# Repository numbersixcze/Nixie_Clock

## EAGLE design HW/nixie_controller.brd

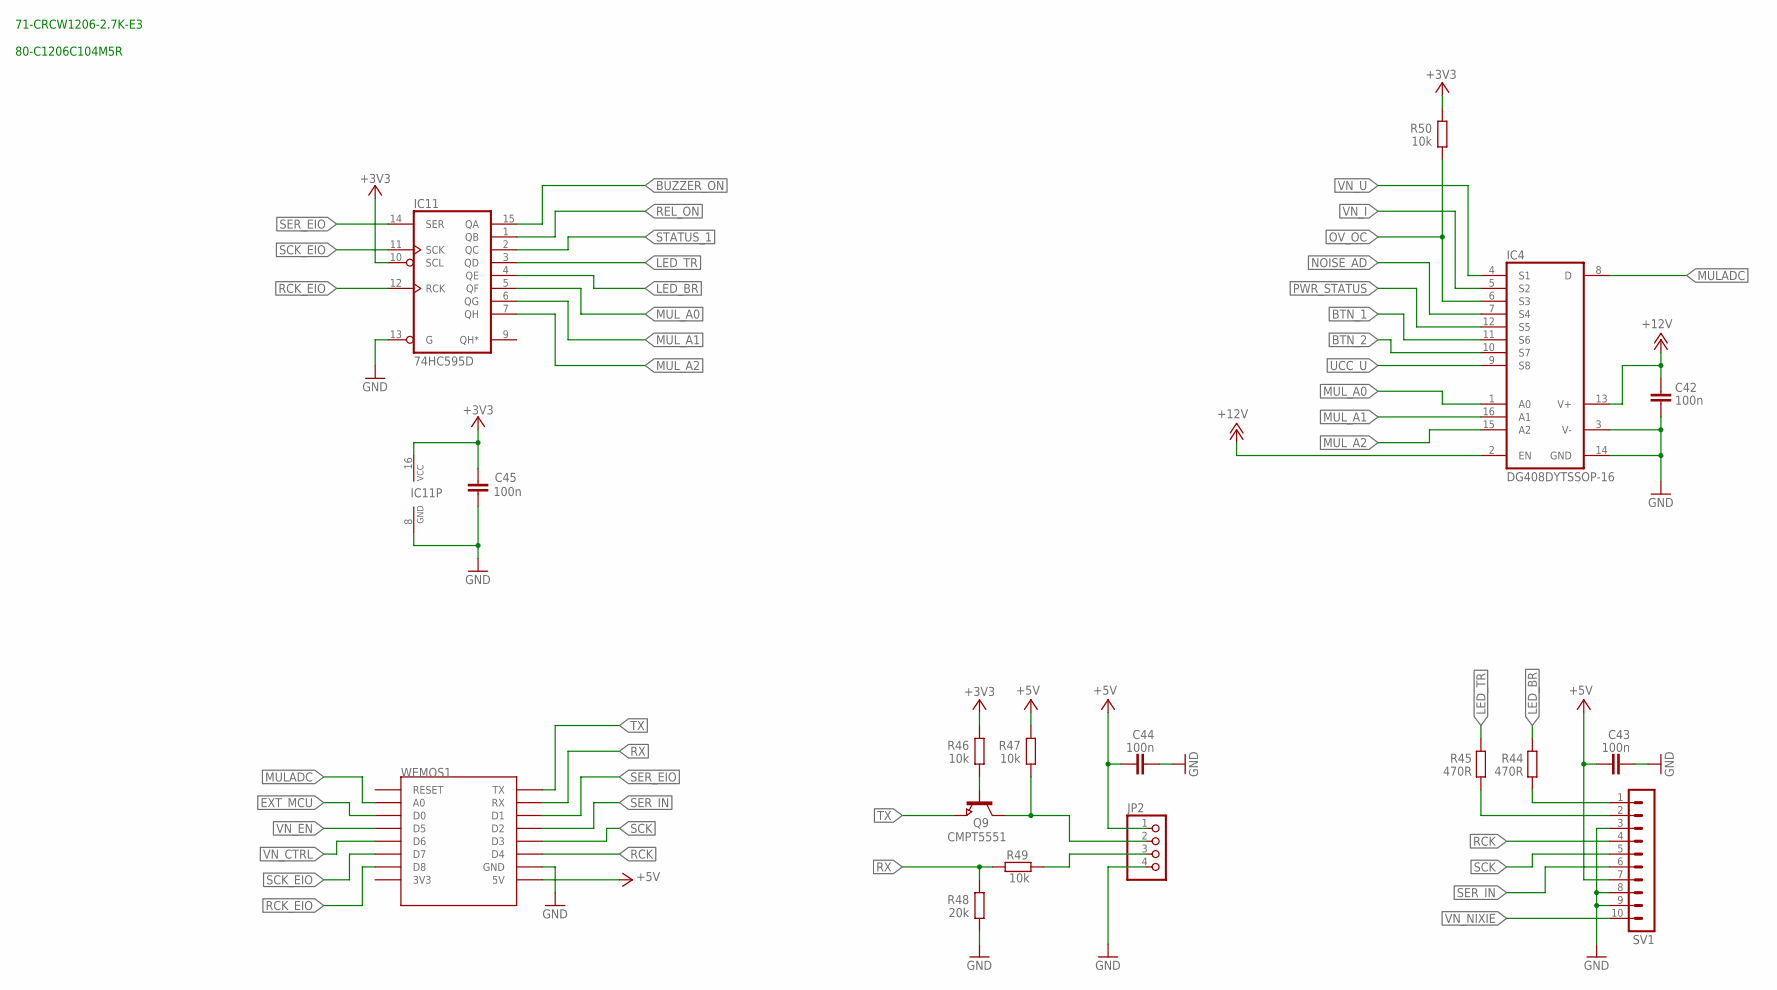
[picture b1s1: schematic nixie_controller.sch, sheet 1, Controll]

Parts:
C42, C43, C44, C45: 100n; C1206
IC4: DG408DYTSSOP-16; TSSOP16
IC11: 74HC595D; SO16
JP2: PINHD-1X4/90; 1X04/90
Q9: CMPT5551; SOT23
R44, R45: 470R; R1206
R46, R47, R49, R50: 10k; R1206
R48: 20k; R1206
SV1: MA10-1
WEMOS1: WEMOS-D1-MINI

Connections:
+3V3: C45.1, IC11.10 (SCL), IC11.16 (VCC), R46.1, R50.1; also elsewhere on the board
+5V: C43.1, C44.1, JP2.1, R47.1, SV1.7, WEMOS1.5V; also elsewhere on the board
+12V: C42.1, IC4.2 (EN), IC4.13 (V+); also elsewhere on the board
BTN_1: IC4.11 (S6); also elsewhere on the board
BTN_2: IC4.10 (S7); also elsewhere on the board
BUZZER_ON: IC11.15 (QA); also elsewhere on the board
EXT_MCU: WEMOS1.D0; also elsewhere on the board
GND: C42.2, C43.2, C44.2, C45.2, IC4.3 (V-), IC4.14 (GND), IC11.8 (GND), IC11.13 (G), JP2.4, R48.2, SV1.3, SV1.8, SV1.9, WEMOS1.GND; also elsewhere on the board
LED_B: R45.2, SV1.2
LED_BR: IC11.4 (QE), R44.1
LED_T: R44.2, SV1.1
LED_TR: IC11.3 (QD), R45.1
MULADC: IC4.8 (D), WEMOS1.A0
MUL_A0: IC4.1 (A0), IC11.5 (QF)
MUL_A1: IC4.16 (A1), IC11.6 (QG)
MUL_A2: IC4.15 (A2), IC11.7 (QH)
unnamed: Q9.1 (B), R46.2
NOISE_AD: IC4.7 (S4); also elsewhere on the board
OV_OC: IC4.6 (S3), R50.2; also elsewhere on the board
PWR_STATUS: IC4.12 (S5); also elsewhere on the board
RCK: SV1.4, WEMOS1.D4
RCK_EIO: IC11.12 (RCK), WEMOS1.D8
REL_ON: IC11.1 (QB); also elsewhere on the board
RX: R48.1, R49.1, WEMOS1.RX
RX_IN: JP2.3, R49.2
SCK: SV1.5, WEMOS1.D3
SCK_EIO: IC11.11 (SCK), WEMOS1.D7
SER_EIO: IC11.14 (SER), WEMOS1.D1
SER_IN: SV1.6, WEMOS1.D2
STATUS_1: IC11.2 (QC); also elsewhere on the board
TX: Q9.2 (E), WEMOS1.TX
TX_IN: JP2.2, Q9.3 (C), R47.2
UCC_U: IC4.9 (S8); also elsewhere on the board
VN_CTRL: WEMOS1.D6; also elsewhere on the board
VN_EN: WEMOS1.D5; also elsewhere on the board
VN_I: IC4.5 (S2); also elsewhere on the board
VN_NIXIE: SV1.10; also elsewhere on the board
VN_U: IC4.4 (S1); also elsewhere on the board

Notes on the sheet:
71-CRCW1206-2.7K-E3 80-C1206C104M5R

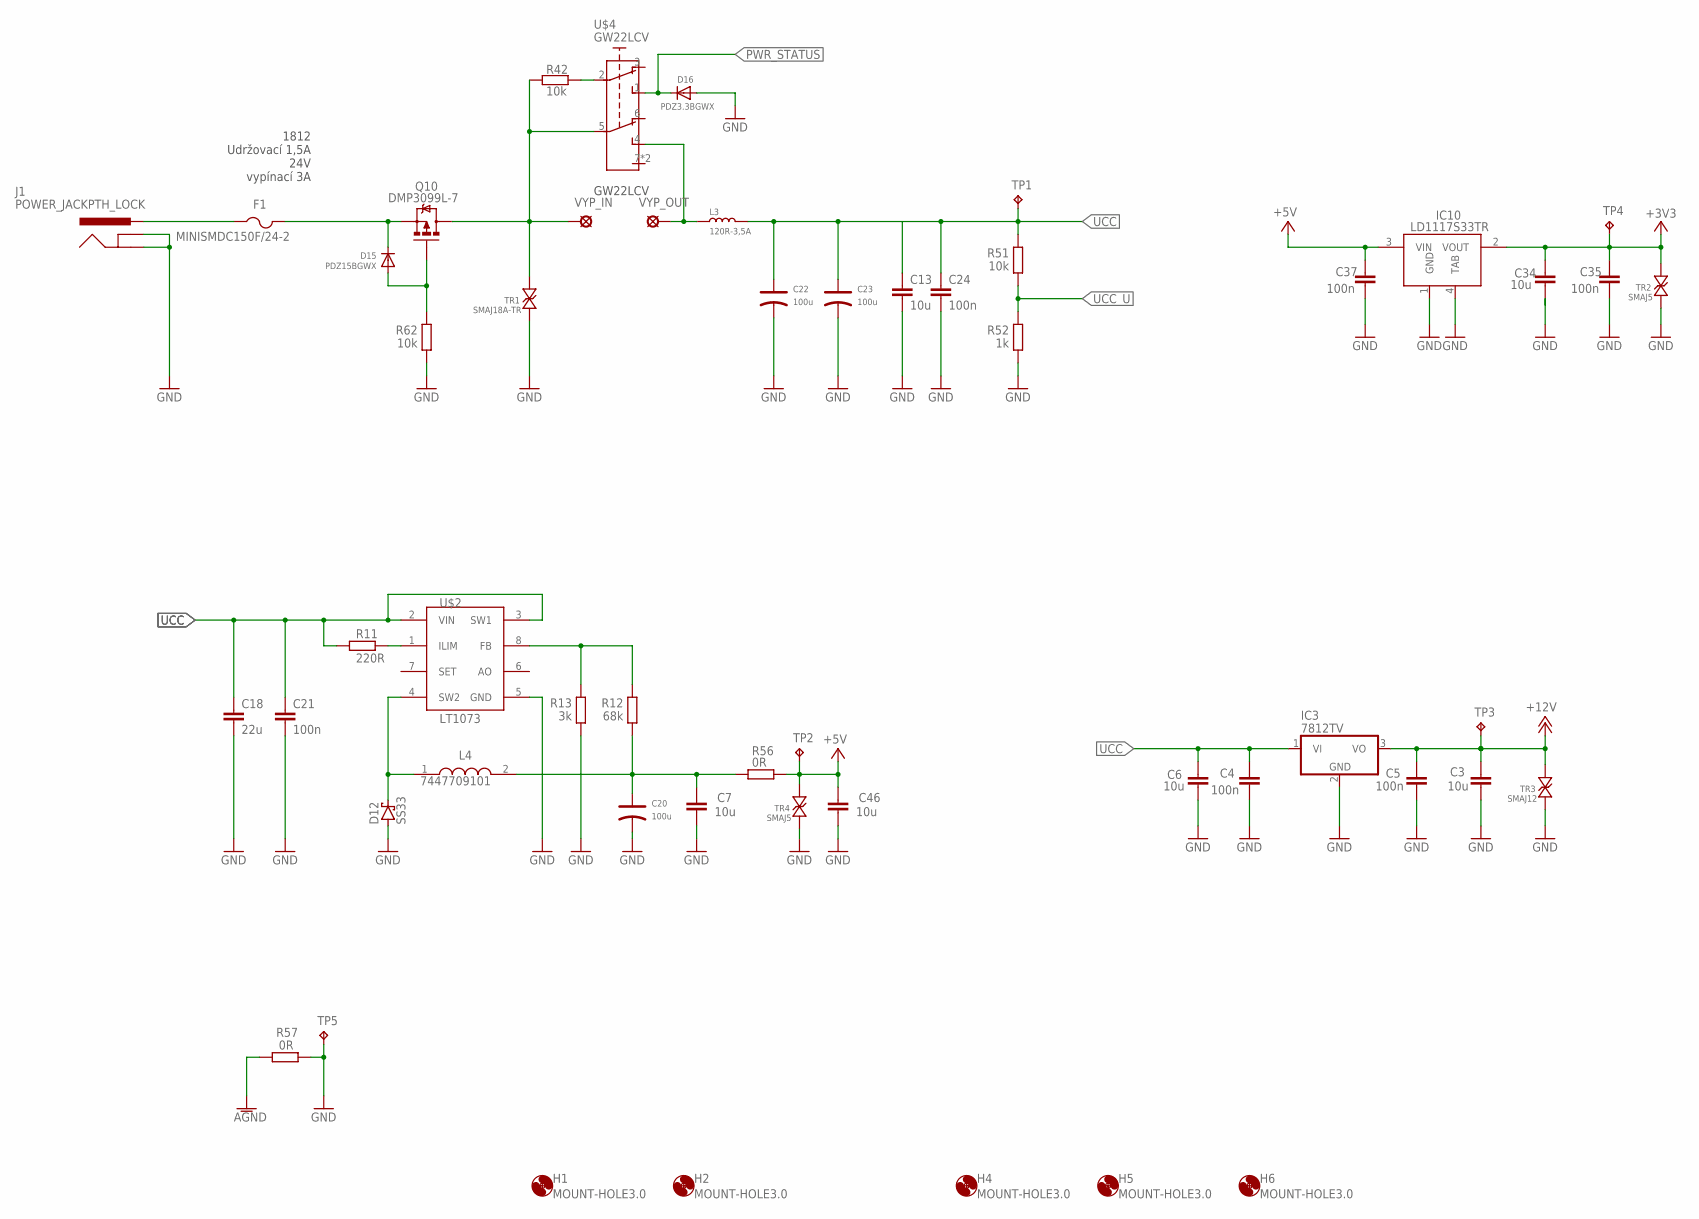
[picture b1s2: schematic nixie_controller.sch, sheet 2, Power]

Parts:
C3, C6, C7, C13, C34, C46: 10u; C1206
C4, C5, C21, C24, C35, C37: 100n; C1206
C18: 22u; C1206
C20, C22, C23: 100u; ELECTRO-SMD-C-6MM
D12: SS33; SMC
D15: PDZ15BGWX; SOD-123
D16: PDZ3.3BGWX; SOD-123
F1: MINISMDC150F/24-2; 1812
H1, H2, H4, H5, H6: MOUNT-HOLE3.0; 3,0
IC3: 7812TV; TO220V
IC10: LD1117S33TR; SOT230P700X180-4N
J1: POWER_JACKPTH_LOCK; POWER_JACK_PTH_LOCK
L3: 120R-3,5A; L0805
L4: 7447709101; INDM120120X1000N
Q10: DMP3099L-7; SOT23-3
R11: 220R; R1206
R12: 68k; R1206
R13: 3k; R1206
R42, R51, R62: 10k; R1206
R52: 1k; R1206
R56, R57: 0R; R1206
TP1, TP2, TP3, TP4, TP5: TPB1,27; B1,27
TR1: SMAJ18A-TR; DO214AC+MINIMELF_BIDIR
TR2, TR4: SMAJ5; DO214AC+MINIMELF_BIDIR
TR3: SMAJ12; DO214AC+MINIMELF_BIDIR
U$2: LT1073; SOIC127P599X175-8
U$4: GW22LCV
VYP_IN: LSP11
VYP_OUT: LSP11

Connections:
+3V3: C34.1, C35.1, IC10.2 (VOUT), TP4.TP, TR2.P$2; also elsewhere on the board
+5V: C37.1, C46.1, IC10.3 (VIN), R56.1, TP2.TP, TR4.P$2; also elsewhere on the board
+12V: C3.1, C5.1, IC3.3 (VO), TP3.TP, TR3.P$2; also elsewhere on the board
AGND: R57.2; also elsewhere on the board
GND: C3.2, C4.2, C5.2, C6.2, C7.2, C13.2, C18.2, C20.-, C21.2, C22.-, C23.-, C24.2, C34.2, C35.2, C37.2, C46.2, D12.A, D16.A, IC3.2 (GND), IC10.1 (GND), IC10.4 (TAB), J1.GND, J1.GNDBREAK, R13.1, R52.1, R57.1, R62.1, TP5.TP, TR1.P$1, TR2.P$1, TR3.P$1, TR4.P$1, U$2.5 (GND); also elsewhere on the board
unnamed: D12.C, L4.1, U$2.4 (SW2)
unnamed: F1.1, J1.PWR
unnamed: L3.1, U$4.4 (NO1), VYP_OUT.MP
unnamed: R11.2, U$2.1 (ILIM)
unnamed: R12.2, R13.2, U$2.8 (FB)
unnamed: Q10.3 (D), R42.2, TR1.P$2, U$4.5 (COM1), VYP_IN.MP
unnamed: C7.1, C20.+, L4.2, R12.1, R56.2
unnamed: D15.C, F1.2, Q10.2 (S)
unnamed: R42.1, U$4.2 (COM)
unnamed: D15.A, Q10.1 (G), R62.2
P$1: U$4.7, U$4.8
PWR_STATUS: D16.C, U$4.1 (NO); also elsewhere on the board
UCC: C4.1, C6.1, C13.1, C18.1, C21.1, C22.+, C23.+, C24.1, IC3.1 (VI), L3.2, R11.1, R51.2, TP1.TP, U$2.2 (VIN), U$2.3 (SW1); also elsewhere on the board
UCC_U: R51.1, R52.2; also elsewhere on the board

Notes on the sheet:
1812 Udržovací 1,5A 24V vypínací 3A
GW22LCV

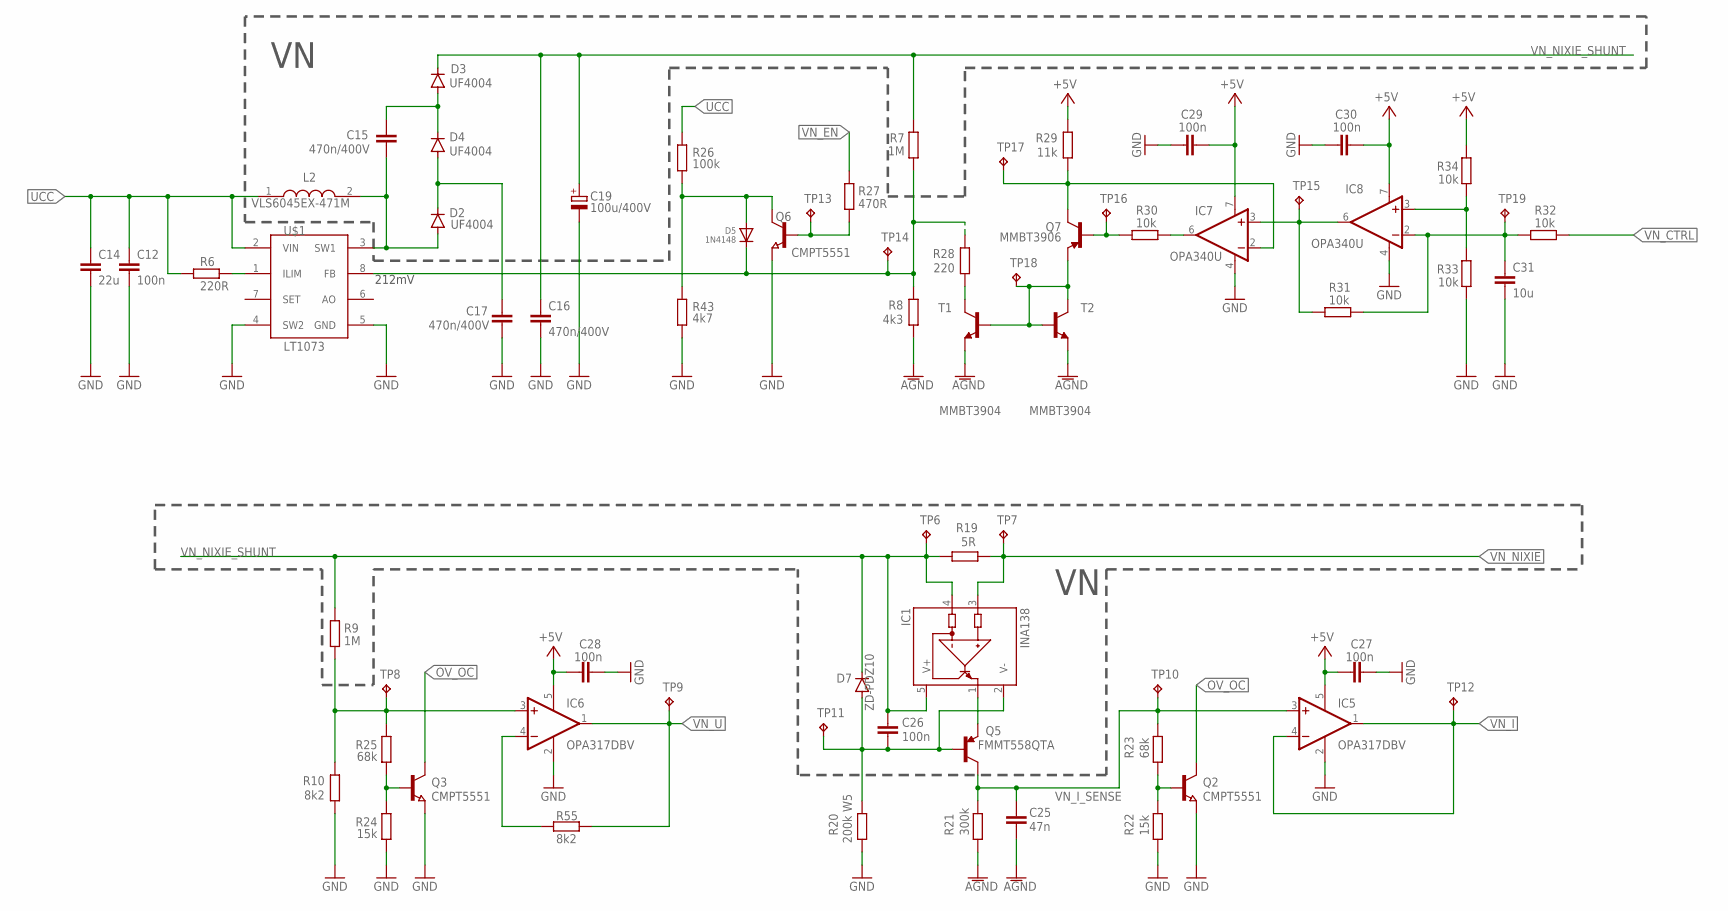
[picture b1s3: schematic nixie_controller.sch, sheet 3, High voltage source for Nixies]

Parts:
C12, C26, C27, C28, C29, C30: 100n; C1206
C14: 22u; C1206
C15, C16, C17: 470n/400V; C1812
C19: 100u/400V; E51-22
C25: 47n; C1206
C31: 10u; C1206
D2, D3, D4: UF4004; DO41-10
D5: 1N4148; SOD-123
D7: ZD-PDZ10; SOD123
IC1: INA138; SOT23-5
IC5, IC6: OPA317DBV; SOT23-5
IC7, IC8: OPA340U; SO08
L2: VLS6045EX-471M; INDPM6060X450N
Q2, Q3, Q6: CMPT5551; SOT23
Q5: FMMT558QTA; SOT23-3
Q7: MMBT3906; SOT23-3
R6: 220R; R1206
R7, R9: 1M; R1206
R8: 4k3; R1206
R10, R55: 8k2; R1206
R19: 5R; R1206
R20: 200k W5; R1206
R21: 300k; R1206
R22, R24: 15k; R1206
R23, R25: 68k; R1206
R26: 100k; R1206
R27: 470R; R1206
R28: 220; R1206
R29: 11k; R1206
R30, R31, R32, R33, R34: 10k; R1206
R43: 4k7; R1206
T1, T2: MMBT3904; SOT23-BEC
TP6, TP7, TP8, TP9, TP10, TP11, TP12, TP13, TP14, TP15, TP16, TP17, TP18, TP19: TPB1,27; B1,27
U$1: LT1073; SOIC127P599X175-8

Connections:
+5V: C27.1, C28.1, C29.1, C30.1, IC5.5 (V+), IC6.5 (V+), IC7.7 (V+), IC8.7 (V+), R29.2, R34.1; also elsewhere on the board
AGND: C25.2, R8.1, R21.2, T1.E, T2.E; also elsewhere on the board
GND: C12.2, C14.2, C16.2, C17.2, C19.-, C27.2, C28.2, C29.2, C30.2, C31.2, IC5.2 (V-), IC6.2 (V-), IC7.4 (V-), IC8.4 (V-), Q2.2 (E), Q3.2 (E), Q6.2 (E), R10.1, R20.2, R22.2, R24.2, R33.2, R43.2, U$1.4 (SW2), U$1.5 (GND); also elsewhere on the board
unnamed: IC6.4 (-IN), R55.2
unnamed: R6.2, U$1.1 (ILIM)
unnamed: C15.1, D2.A, L2.2, U$1.3 (SW1)
unnamed: C15.2, D3.A, D4.C
unnamed: C17.1, D2.C, D4.A
unnamed: Q2.1 (B), R22.1, R23.2
unnamed: Q3.1 (B), R24.1, R25.2
unnamed: Q6.1 (B), R27.2, TP13.TP
unnamed: C26.2, D7.A, IC1.2 (V-), Q5.1 (B), R20.1, TP11.TP
unnamed: IC1.1 (OUT), Q5.2 (E)
unnamed: C31.1, IC8.2 (-IN), R31.1, R32.2, TP19.TP
unnamed: R28.1, T1.C
unnamed: Q7.2 (E), T1.B, T2.B, T2.C, TP18.TP
unnamed: IC7.3 (+IN), IC8.6 (OUT), R31.2, TP15.TP
unnamed: IC8.3 (+IN), R33.1, R34.2
unnamed: Q7.1 (B), R30.2, TP16.TP
unnamed: IC7.6 (OUT), R30.1
unnamed: IC7.2 (-IN), Q7.3 (C), R29.1, TP17.TP
unnamed: D5.A, Q6.3 (C), R26.2, R43.1
OV_OC: Q2.3 (C), Q3.3 (C); also elsewhere on the board
SW_FB: D5.C, R7.1, R8.2, R28.2, TP14.TP, U$1.8 (FB)
UCC: C12.1, C14.1, L2.1, R6.1, R26.1, U$1.2 (VIN); also elsewhere on the board
VN_CTRL: R32.1; also elsewhere on the board
VN_EN: R27.1; also elsewhere on the board
VN_I: IC5.1 (OUT), IC5.4 (-IN), TP12.TP; also elsewhere on the board
VN_I_SENSE: C25.1, IC5.3 (+IN), Q5.3 (C), R21.1, R23.1, TP10.TP
VN_NIXIE: IC1.3 (IN+), R19.1, TP7.TP; also elsewhere on the board
VN_NIXIE_SHUNT: C16.1, C19.+, C26.1, D3.C, D7.C, IC1.4 (IN-), IC1.5 (V+), R7.2, R9.2, R19.2, TP6.TP
VN_U: IC6.1 (OUT), R55.1, TP9.TP; also elsewhere on the board
VN_U_SENSE: IC6.3 (+IN), R9.1, R10.2, R25.1, TP8.TP

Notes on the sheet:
212mV

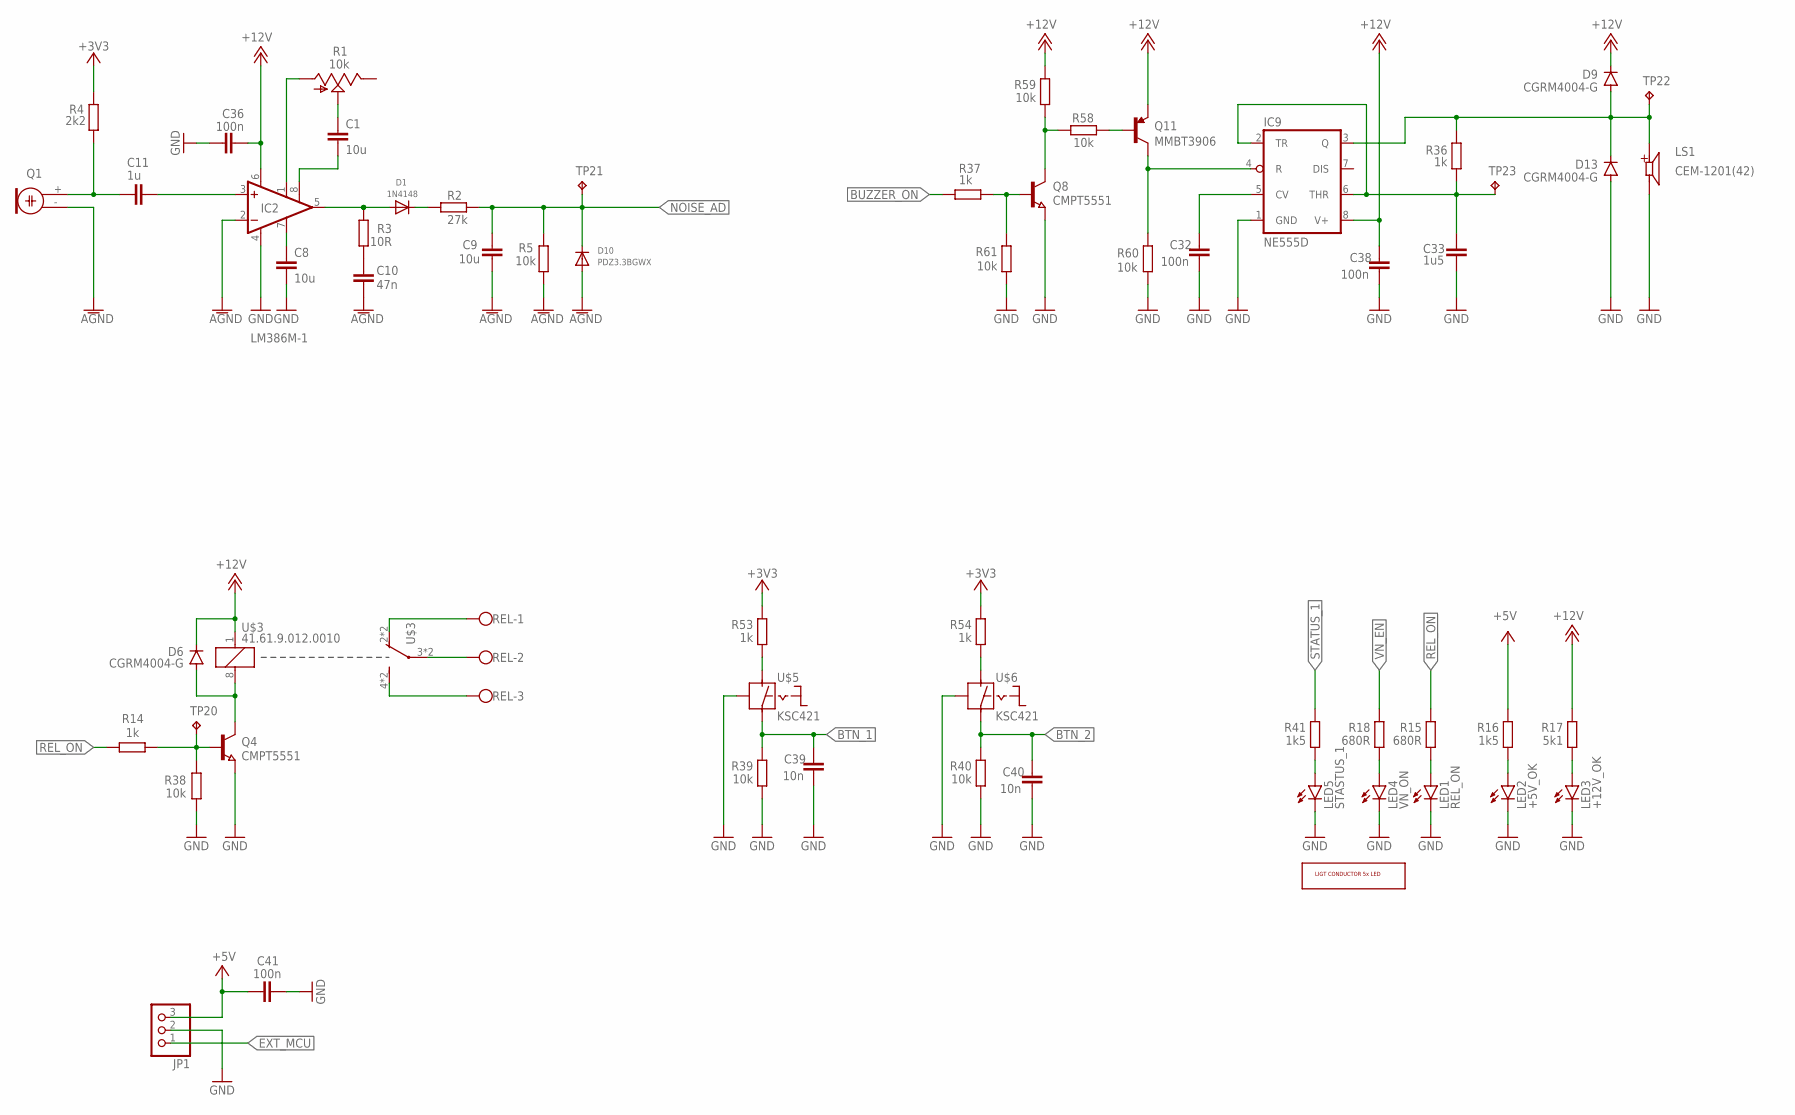
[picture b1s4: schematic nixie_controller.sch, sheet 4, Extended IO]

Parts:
C1, C8, C9: 10u; C1206
C10: 47n; C1206
C11: 1u; C1206
C32, C36, C38, C41: 100n; C1206
C33: 1u5; C1206
C39, C40: 10n; C1206
D1: 1N4148; SOD-123
D6, D9, D13: CGRM4004-G; SOD-123_MINI-SMA
D10: PDZ3.3BGWX; SOD-123
IC2: LM386M-1; SO08
IC9: NE555D; SO08
JP1: PINHD-1X3/90; 1X03/90
LED1: REL_ON; CHIP-LED0805
LED2: +5V_OK; CHIP-LED0805
LED3: +12V_OK; CHIP-LED0805
LED4: VN_ON; CHIP-LED0805
LED5: STASTUS_1; CHIP-LED0805
LS1: CEM-1201(42); CUI_CEM-1201(42)
Q1: ELECTRET; 9.7ELECTRET
Q4, Q8: CMPT5551; SOT23
Q11: MMBT3906; SOT23-3
R1: 10k; RJ9W
R2: 27k; R1206
R3: 10R; R1206
R4: 2k2; R1206
R5, R38, R39, R40, R58, R59, R60, R61: 10k; R1206
R14, R36, R37, R53, R54: 1k; R1206
R15, R18: 680R; R1206
R16, R41: 1k5; R1206
R17: 5k1; R1206
REL: W237-103
TP20, TP21, TP22, TP23: TPB1,27; B1,27
U$3: 41.61.9.012.0010; 41.52
U$5, U$6: KSC421; KSC421V
U$7: LIGT_CONDUCT_5LED; LC_5LED

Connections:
+3V3: R4.2, R53.2, R54.2; also elsewhere on the board
+5V: C41.2, JP1.3, R16.2; also elsewhere on the board
+12V: C36.2, C38.1, D6.C, D9.C, IC2.6 (VS), IC9.8 (V+), Q11.2 (E), R17.2, R59.2, U$3.1; also elsewhere on the board
AGND: C9.2, C10.2, D10.A, IC2.2 (-IN), Q1.- (1), R5.1; also elsewhere on the board
BTN_1: C39.1, R39.2, U$5.P$1; also elsewhere on the board
BTN_2: C40.1, R40.2, U$6.P$1; also elsewhere on the board
BUZZER_ON: R37.2; also elsewhere on the board
EXT_MCU: JP1.1; also elsewhere on the board
GND: C8.2, C32.2, C33.2, C36.1, C38.2, C39.2, C40.2, C41.1, D13.A, IC2.4 (GND), IC9.1 (GND), JP1.2, LED1.C, LED2.C, LED3.C, LED4.C, LED5.C, LS1.M, Q4.2 (E), Q8.2 (E), R38.2, R39.1, R40.1, R60.1, R61.1, U$5.P$3 (GND), U$5.P$4 (GND), U$5.P$5 (GND), U$5.P$6 (GND), U$5.P$7 (GND), U$5.P$8 (GND), U$6.P$3 (GND), U$6.P$4 (GND), U$6.P$5 (GND), U$6.P$6 (GND), U$6.P$7 (GND), U$6.P$8 (GND); also elsewhere on the board
unnamed: D1.C, R2.1
unnamed: C33.1, IC9.2 (TR), IC9.6 (THR), R36.1, TP23.TP
unnamed: R53.1, U$5.P$2 (S)
unnamed: R54.1, U$6.P$2 (S)
unnamed: D6.A, Q4.3 (C), U$3.8 (2)
unnamed: REL.1, U$3.2 (O), U$3.7 (O)
unnamed: REL.2, U$3.3, U$3.6
unnamed: C8.1, IC2.7 (BYPASS)
unnamed: C10.1, R3.1
unnamed: C11.1, Q1.+ (2), R4.1
unnamed: C1.2, IC2.8 (GAIN)
unnamed: IC2.1 (GAIN), R1.A
unnamed: C1.1, R1.S
unnamed: C11.2, IC2.3 (+IN)
unnamed: LED2.A, R16.1
unnamed: D1.A, IC2.5 (OUT), R3.2
unnamed: REL.3, U$3.4 (S), U$3.5 (S)
unnamed: LED3.A, R17.1
unnamed: Q4.1 (B), R14.1, R38.1, TP20.TP
unnamed: LED1.A, R15.1
unnamed: IC9.4 (R), Q11.3 (C), R60.2
unnamed: LED4.A, R18.1
unnamed: C32.1, IC9.5 (CV)
unnamed: Q11.1 (B), R58.2
unnamed: D9.A, D13.C, IC9.3 (Q), LS1.P, R36.2, TP22.TP
unnamed: Q8.3 (C), R58.1, R59.1
unnamed: LED5.A, R41.1
unnamed: Q8.1 (B), R37.1, R61.2
NOISE_AD: C9.1, D10.C, R2.2, R5.2, TP21.TP; also elsewhere on the board
REL_ON: R14.2, R15.2; also elsewhere on the board
STATUS_1: R41.2; also elsewhere on the board
VN_EN: R18.2; also elsewhere on the board

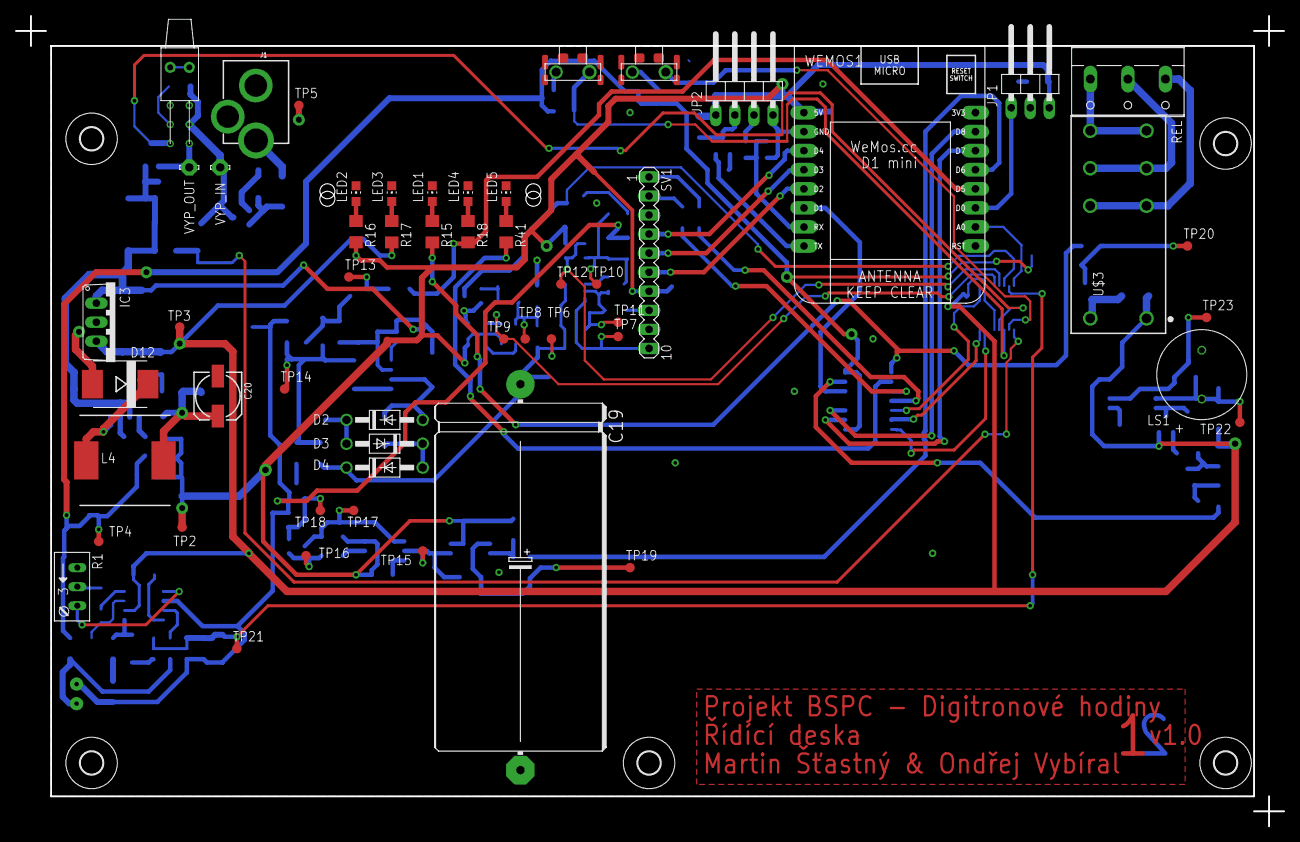
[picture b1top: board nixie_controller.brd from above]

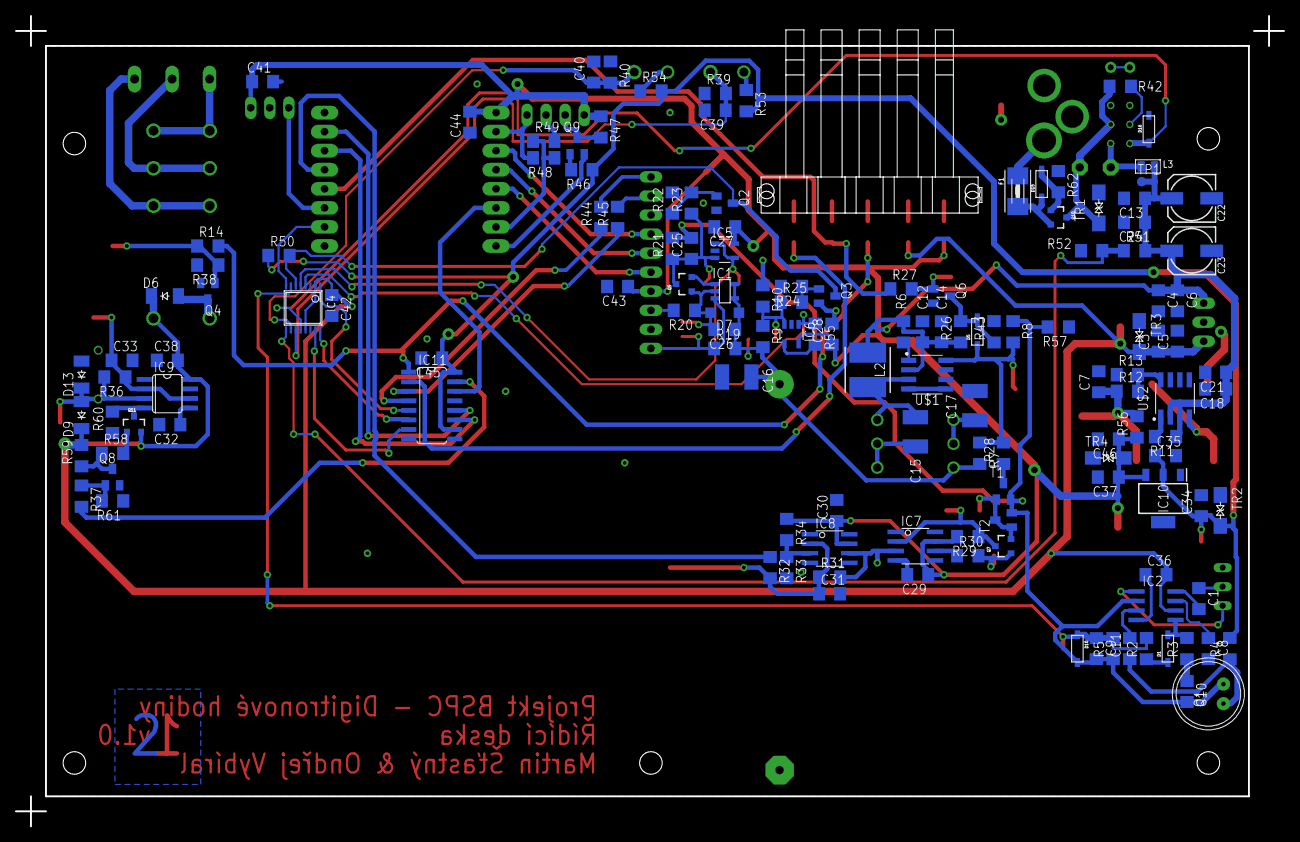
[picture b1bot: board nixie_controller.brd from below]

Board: 2 copper layers, 169.0 x 108.0 mm, 200 parts (140 on the bottom side), 102 nets.

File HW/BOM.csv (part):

"Qty";"Value";"Device";"Package";"Parts";"Description";"DESCRIPTION";"HEIGHT";"MANUFACTURER";"MANUFACTURER_NAME";"MANUFACTURER_PART_NUMBER";"MF";"MOUSER_PART_NUMBER";"MOUSER_PRICE-STOCK";"MPN";"OC_FARNELL";"OC_NEWARK";"PROD_ID";"RS_PART_NUMBER";"RS_PRICE-STOCK";"SF_ID";"SPICEPREFIX";"STANDARD";"TP_SIGNAL_NAME";"VALUE";
"1";"";"ELECTRET";"9.7ELECTRET";"Q1";"Electret microphone";"";"";"";"";"";"";"";"";"";"";"";"";"";"";"";"";"";"";"";
"1";"";"MA10-1";"MA10-1";"SV1";"PIN HEADER";"";"";"";"";"";"";"";"";"";"unknown";"unknown";"";"";"";"";"";"";"";"";
"1";"";"PINHD-1X3/90";"1X03/90";"JP1";"PIN HEADER";"";"";"";"";"";"";"";"";"";"";"";"";"";"";"";"";"";"";"";
"1";"";"PINHD-1X4/90";"1X04/90";"JP2";"PIN HEADER";"";"";"";"";"";"";"";"";"";"";"";"";"";"";"";"";"";"";"";
"1";"";"W237-103";"W237-103";"REL";"WAGO SCREW CLAMP";"";"";"";"";"";"";"";"";"237-103";"unknown";"18M7116";"";"";"";"";"";"";"";"";
"1";"";"WEMOS-D1-MINI";"WEMOS-D1-MINI";"WEMOS1";"WeMos.cc";"";"";"";"";"";"";"";"";"";"";"";"";"";"";"";"";"";"";"";
"1";"+12V_OK";"LEDCHIP-LED0805";"CHIP-LED0805";"LED3";"LED";"";"";"";"";"";"";"";"";"";"";"";"";"";"";"";"";"";"";"";
"1";"+5V_OK";"LEDCHIP-LED0805";"CHIP-LED0805";"LED2";"LED";"";"";"";"";"";"";"";"";"";"";"";"";"";"";"";"";"";"";"";
"2";"0R";"R-EU_R1206";"R1206";"R56, R57";"RESISTOR, European symbol";"";"";"";"";"";"";"";"";"";"";"";"";"";"";"";"R";"";"";"";
"1";"100k";"R-EU_R1206";"R1206";"R26";"RESISTOR, European symbol";"";"";"";"";"";"";"";"";"";"";"";"";"";"";"";"R";"";"";"";
"20";"100n";"C-EUC1206";"C1206";"C4, C5, C12, C21, C24, C26, C27, C28, C29, C30, C32, C35, C36, C37, C38, C41, C42, C43, C44, C45";"CAPACITOR, European symbol";"";"";"";"";"";"";"";"";"";"";"";"";"";"";"";"C";"";"";"";
"3";"100u";"ALUMINUM-SMD-220UF-16V(D6.3-H7.7MM)";"ELECTRO-SMD-C-6MM";"C20, C22, C23";"302030053";"";"";"";"";"";"";"";"";"CS1E221M-CRE77";"";"";"";"";"";"";"";"";"";"220UF";
"1";"100u/400V";"CPOL_E51X21";"E51-22";"C19";"";"";"";"";"";"";"";"";"";"";"";"";"";"";"";"";"";"";"";"";
"1";"10R";"R-EU_R1206";"R1206";"R3";"RESISTOR, European symbol";"";"";"";"";"";"";"";"";"";"";"";"";"";"";"";"R";"";"";"";
"20";"10k";"R-EU_R1206";"R1206";"R5, R30, R31, R32, R33, R34, R38, R39, R40, R42, R46, R47, R49, R50, R51, R58, R59, R60, R61, R62";"RESISTOR, European symbol";"";"";"";"";"";"";"";"";"";"";"";"";"";"";"";"R";"";"";"";
"1";"10k";"TRIM_US-RJ9W";"RJ9W";"R1";"POTENTIOMETER";"";"";"";"";"";"";"";"";"";"";"";"";"";"";"";"";"";"";"";
"2";"10n";"C-EUC1206";"C1206";"C39, C40";"CAPACITOR, European symbol";"";"";"";"";"";"";"";"";"";"";"";"";"";"";"";"C";"";"";"";
"10";"10u";"C-EUC1206";"C1206";"C1, C3, C6, C7, C8, C9, C13, C31, C34, C46";"CAPACITOR, European symbol";"";"";"";"";"";"";"";"";"";"";"";"";"";"";"";"C";"";"";"";
"1";"11k";"R-EU_R1206";"R1206";"R29";"RESISTOR, European symbol";"";"";"";"";"";"";"";"";"";"";"";"";"";"";"";"R";"";"";"";
"1";"120R-3,5A";"SMD-FERRITE-BEAD-470R-2A(0805)'0805'";"L0805";"L3";"303030008";"";"";"";"";"";"";"";"";"WLB2012-471T20";"";"";"";"";"";"";"";"";"";"470R-2A";
"2";"15k";"R-EU_R1206";"R1206";"R22, R24";"RESISTOR, European symbol";"";"";"";"";"";"";"";"";"";"";"";"";"";"";"";"R";"";"";"";
"2";"1M";"R-EU_R1206";"R1206";"R7, R9";"RESISTOR, European symbol";"";"";"";"";"";"";"";"";"";"";"";"";"";"";"";"R";"";"";"";
"2";"1N4148";"DIODESOD-123";"SOD-123";"D1, D5";"Diode";"";"";"";"";"";"";"";"";"";"";"";"";"";"";"";"";"";"";"";
"6";"1k";"R-EU_R1206";"R1206";"R14, R36, R37, R52, R53, R54";"RESISTOR, European symbol";"";"";"";"";"";"";"";"";"";"";"";"";"";"";"";"R";"";"";"";
"2";"1k5";"R-EU_R1206";"R1206";"R16, R41";"RESISTOR, European symbol";"";"";"";"";"";"";"";"";"";"";"";"";"";"";"";"R";"";"";"";
"1";"1u";"C-EUC1206";"C1206";"C11";"CAPACITOR, European symbol";"";"";"";"";"";"";"";"";"";"";"";"";"";"";"";"C";"";"";"";
"1";"1u5";"C-EUC1206";"C1206";"C33";"CAPACITOR, European symbol";"";"";"";"";"";"";"";"";"";"";"";"";"";"";"";"C";"";"";"";
"1";"200k W5";"R-EU_R1206";"R1206";"R20";"RESISTOR, European symbol";"";"";"";"";"";"";"";"";"";"";"";"";"";"";"";"R";"";"";"";
"1";"20k";"R-EU_R1206";"R1206";"R48";"RESISTOR, European symbol";"";"";"";"";"";"";"";"";"";"";"";"";"";"";"";"R";"";"";"";
"1";"220";"R-EU_R1206";"R1206";"R28";"RESISTOR, European symbol";"";"";"";"";"";"";"";"";"";"";"";"";"";"";"";"R";"";"";"";
"2";"220R";"R-EU_R1206";"R1206";"R6, R11";"RESISTOR, European symbol";"";"";"";"";"";"";"";"";"";"";"";"";"";"";"";"R";"";"";"";
"2";"22u";"C-EUC1206";"C1206";"C14, C18";"CAPACITOR, European symbol";"";"";"";"";"";"";"";"";"";"";"";"";"";"";"";"C";"";"";"";
"1";"27k";"R-EU_R1206";"R1206";"R2";"RESISTOR, European symbol";"";"";"";"";"";"";"";"";"";"";"";"";"";"";"";"R";"";"";"";
"1";"2k2";"R-EU_R1206";"R1206";"R4";"RESISTOR, European symbol";"";"";"";"";"";"";"";"";"";"";"";"";"";"";"";"R";"";"";"";
"1";"300k";"R-EU_R1206";"R1206";"R21";"RESISTOR, European symbol";"";"";"";"";"";"";"";"";"";"";"";"";"";"";"";"R";"";"";"";
"1";"3k";"R-EU_R1206";"R1206";"R13";"RESISTOR, European symbol";"";"";"";"";"";"";"";"";"";"";"";"";"";"";"";"R";"";"";"";
"1";"41.61.9.012.0010";"41.61.9.012.0010";"41.52";"U$3";"";"";"";"";"";"";"";"";"";"";"";"";"";"";"";"";"";"";"";"";
"3";"470R";"R-EU_R1206";"R1206";"R27, R44, R45";"RESISTOR, European symbol";"";"";"";"";"";"";"";"";"";"";"";"";"";"";"";"R";"";"";"";
"3";"470n/400V";"C-EUC1812";"C1812";"C15, C16, C17";"CAPACITOR, European symbol";"";"";"";"";"";"";"";"";"";"";"";"";"";"";"";"C";"";"";"";
"2";"47n";"C-EUC1206";"C1206";"C10, C25";"CAPACITOR, European symbol";"";"";"";"";"";"";"";"";"";"";"";"";"";"";"";"C";"";"";"";
"1";"4k3";"R-EU_R1206";"R1206";"R8";"RESISTOR, European symbol";"";"";"";"";"";"";"";"";"";"";"";"";"";"";"";"R";"";"";"";
"1";"4k7";"R-EU_R1206";"R1206";"R43";"RESISTOR, European symbol";"";"";"";"";"";"";"";"";"";"";"";"";"";"";"";"R";"";"";"";
"1";"5R";"R-EU_R1206";"R1206";"R19";"RESISTOR, European symbol";"";"";"";"";"";"";"";"";"";"";"";"";"";"";"";"R";"";"";"";
"1";"5k1";"R-EU_R1206";"R1206";"R17";"RESISTOR, European symbol";"";"";"";"";"";"";"";"";"";"";"";"";"";"";"";"R";"";"";"";
"2";"680R";"R-EU_R1206";"R1206";"R15, R18";"RESISTOR, European symbol";"";"";"";"";"";"";"";"";"";"";"";"";"";"";"";"R";"";"";"";
"3";"68k";"R-EU_R1206";"R1206";"R12, R23, R25";"RESISTOR, European symbol";"";"";"";"";"";"";"";"";"";"";"";"";"";"";"";"R";"";"";"";
"1";"7447709101";"7447709101";"INDM120120X1000N";"L4";"Fixed Inductors WE-PD 1210 100uH 2.5A .11Ohm";"Fixed Inductors WE-PD 1210 100uH 2.5A .11Ohm";"10mm";"";"Wurth Elektronik";"7447709101";"";"710-7447709101";"https://www.mouser.com/Search/Refine.aspx?Keyword=710-7447709101";"";"";"";"";"";"";"";"";"";"";"";
"1";"74HC595D";"74HC595D";"SO16";"IC11";"8-bit SHIFT REGISTER, output latch";"";"";"";"";"";"";"";"";"";"";"";"";"";"";"";"";"";"";"";
"1";"7812TV";"7812TV";"TO220V";"IC3";"Positive VOLTAGE REGULATOR";"";"";"";"";"";"";"";"";"";"";"";"";"";"";"";"";"";"";"";
"2";"8k2";"R-EU_R1206";"R1206";"R10, R55";"RESISTOR, European symbol";"";"";"";"";"";"";"";"";"";"";"";"";"";"";"";"R";"";"";"";
"1";"CEM-1201(42)";"CEM-1201(42)";"CUI_CEM-1201(42)";"LS1";"Audio Buzzer Magnetic 1Vo-p 2Vo-p 20mA 1.5Vo-p 85dBA Pin Through Hole Tray";"";"";"CUI INC";"";"";"";"";"";"";"";"";"";"";"";"";"";"Manufacturer recommendations";"";"";
"3";"CGRM4004-G";"CGRM4004-G";"SOD-123_MINI-SMA";"D6, D9, D13";"Molded plasitc,JEDEC SOD-123/Mini SMA";"";"";"";"";"";"";"";"";"";"";"";"";"";"";"";"";"";"";"";
"6";"CMPT5551";"NPN-TRANSISTOR_SOT23";"SOT23";"Q2, Q3, Q4, Q6, Q8, Q9";"NPN TRANSISTOR";"";"";"";"";"";"";"";"";"";"";"";"";"";"";"";"";"";"";"";
"1";"DG408DYTSSOP-16";"DG408DYTSSOP-16";"TSSOP16";"IC4";"ANALOG MULTIPLEXER";"";"";"";"";"";"";"";"";"";"";"";"";"";"";"";"";"";"";"";
"1";"DMP3099L-7";"MOSFET-PCHANNEL";"SOT23-3";"Q10";"Generic PMOSFET";"";"";"";"";"";"";"";"";"";"";"";"TRANS-08285";"";"";"";"";"";"";"";
"1";"FMMT558QTA";"TRANSISTOR_PNPSMD";"SOT23-3";"Q5";"Generic PNP BJT";"";"";"";"";"";"";"";"";"";"";"";"";"";"";"";"";"";"";"";
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

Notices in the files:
parts and their libraries:
SparkFun-Connectors: Licensing: Creative Commons ShareAlike 4.0 International - https://creativecommons.org/licenses/by-sa/4.0
